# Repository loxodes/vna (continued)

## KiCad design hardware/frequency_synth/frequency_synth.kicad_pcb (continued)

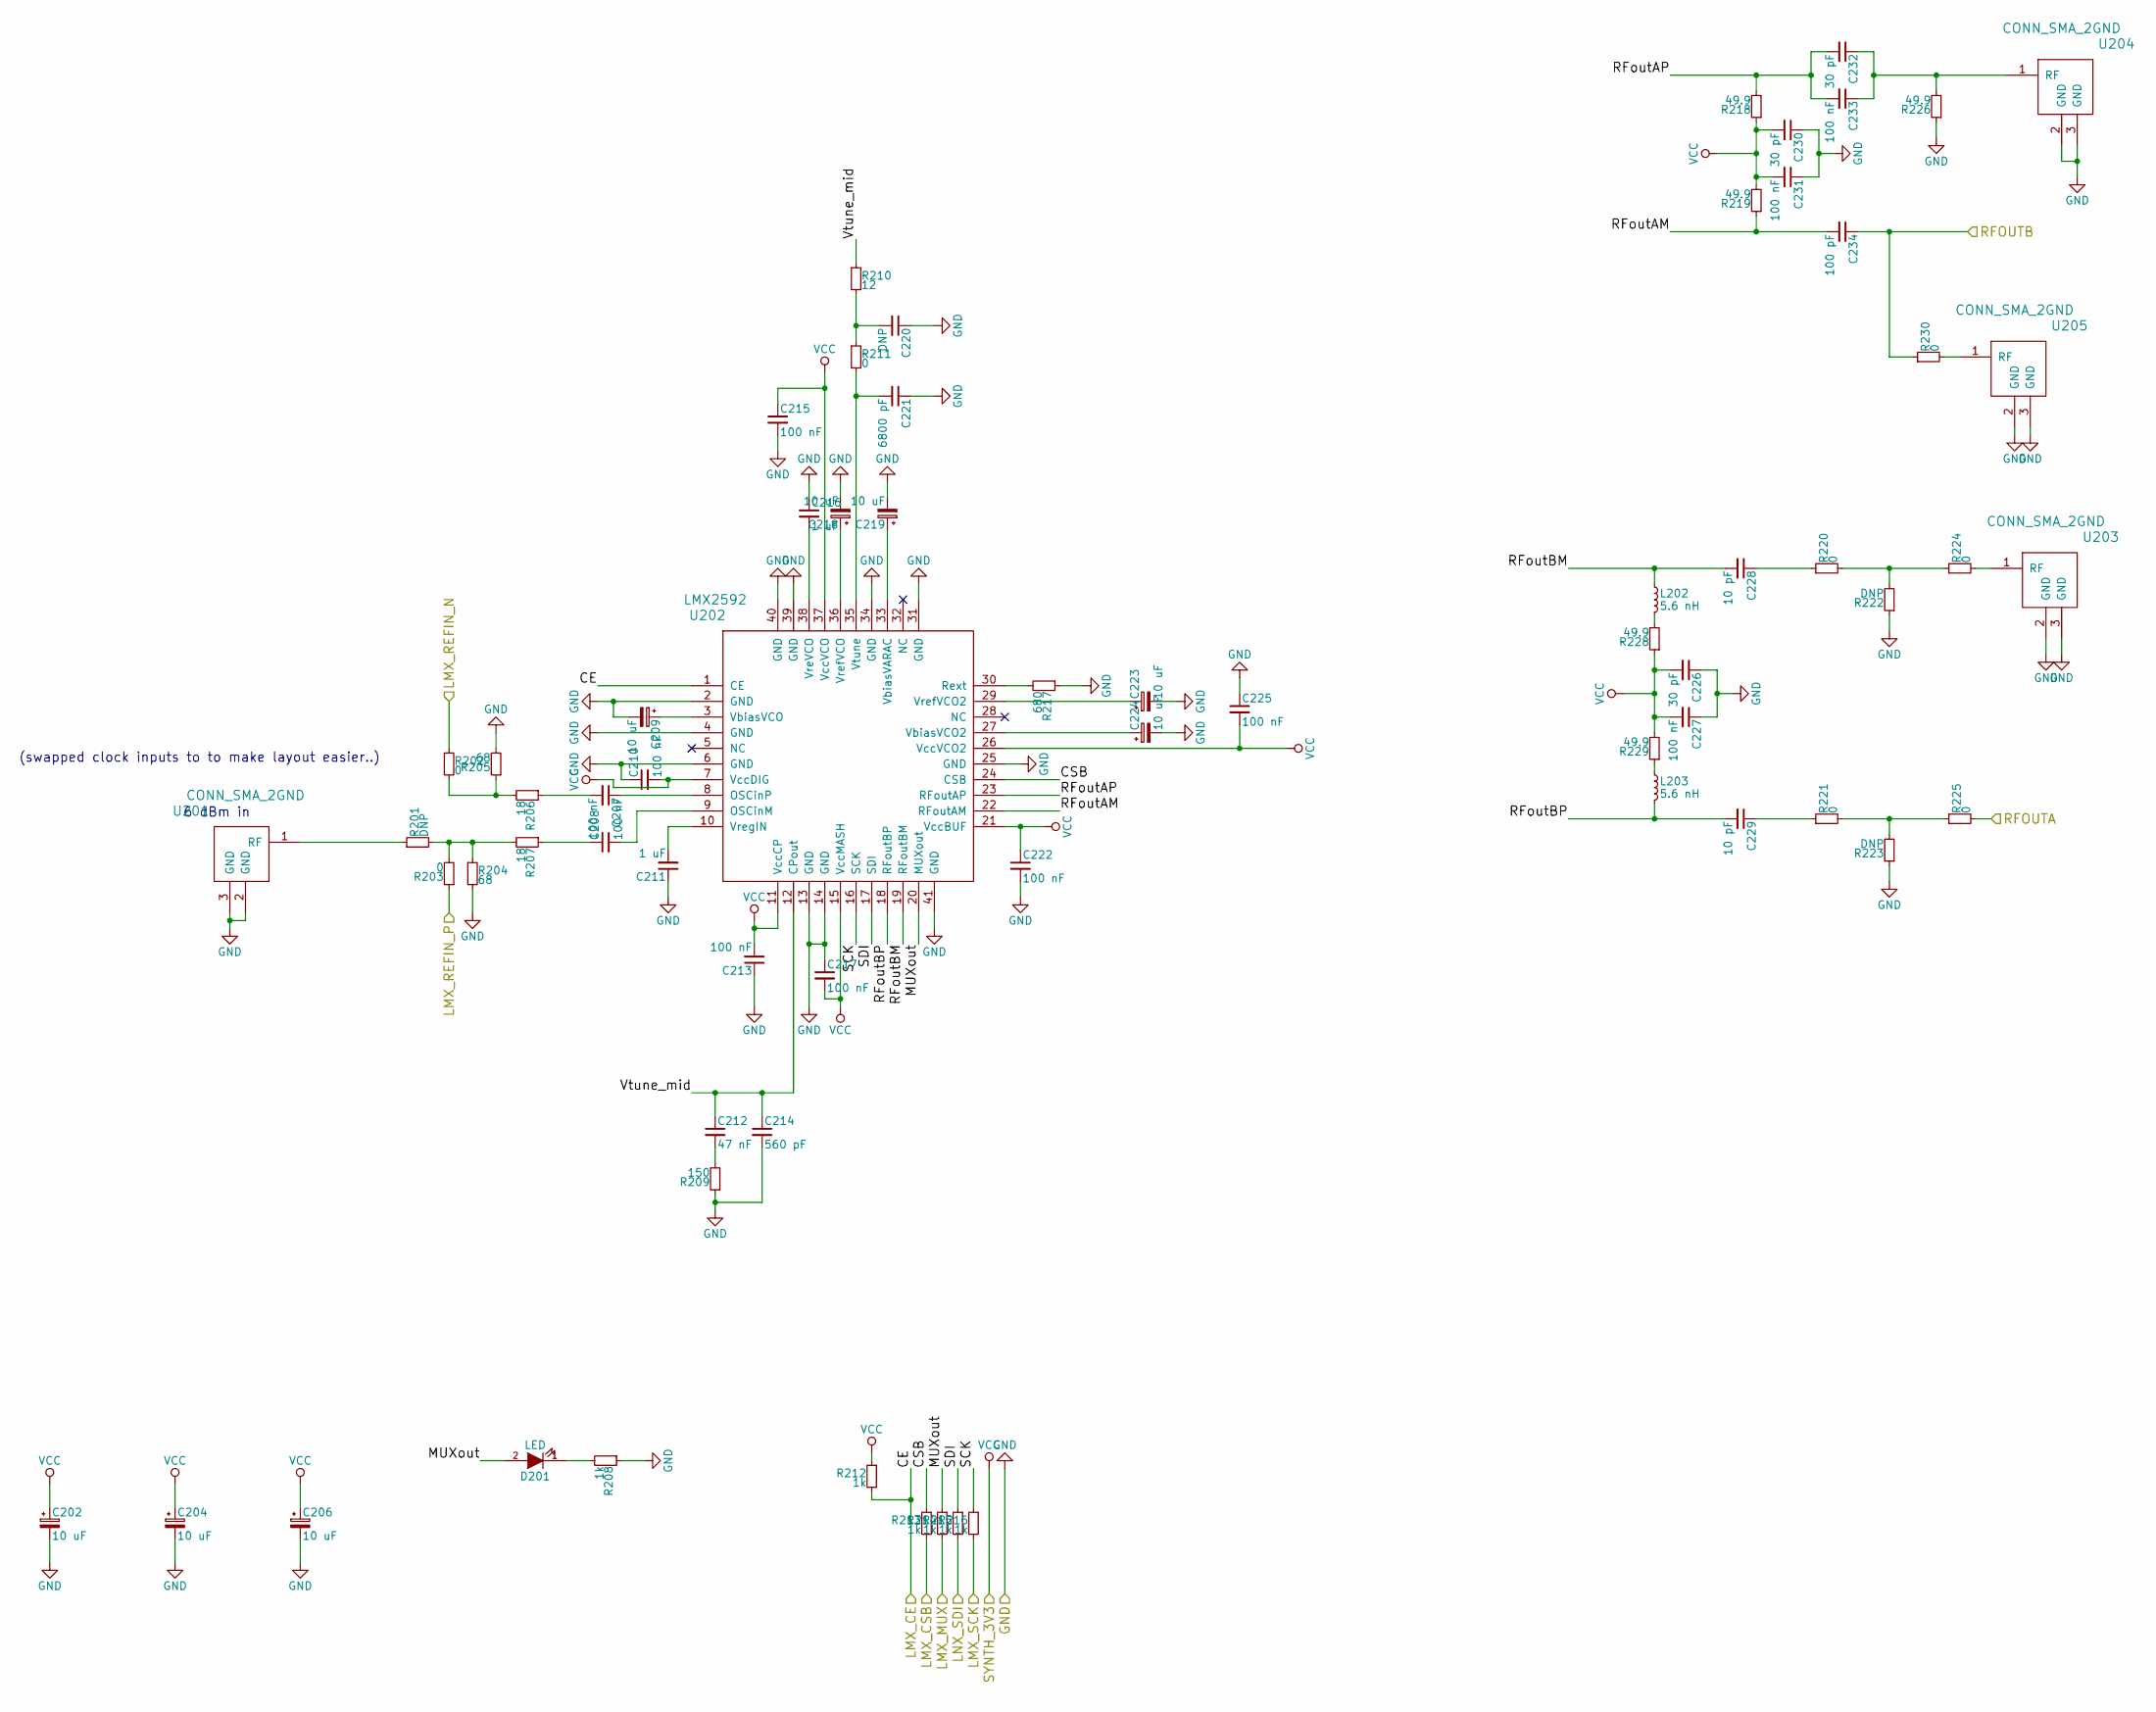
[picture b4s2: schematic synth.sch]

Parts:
C202, C204, C206, C209, C218, C219, C223, C224: 10 uF; C_0603
C207, C208, C210, C213, C215, C217, C222, C225, C227, C231, C233: 100 nF; C_0402
C211, C216: 1 uF; C_0402
C212: 47 nF; C_0402
C214: 560 pF; C_0402
C220: DNP; C_0402
C221: 6800 pF; C_0402
C226, C230, C232: 30 pF; C_0402
C228, C229: 10 pF; C_0402
C234: 100 pF; C_0402
D201: LED; LED_0603
L202, L203: 5.6 nH; R_0402
R201, R222, R223: DNP; R_0402
R202, R203, R211, R220, R221, R224, R225, R230: 0; R_0402
R204, R205: 68; R_0402
R206, R207: 18; R_0402
R208, R212, R213, R214, R215, R216: 1k; R_0402
R209: 150; R_0402
R210: 12; R_0402
R217: 680; R_0402
R218, R219, R226, R228, R229: 49.9; R_0402
U201, U203, U204, U205: CONN_SMA_2GND; 734120110_ufl_umc
U202: LMX2592; QFN-40-1EP_6x6mm_Pitch0.5mm

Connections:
+3V3: C202.1, C204.1, C206.1, C210.2, C213.2, C215.1, C217.2, C222.1, C225.2, C226.2, C227.2, C230.2, C231.2, R212.1, R218.1, R219.2, R228.1, R229.2, U202.7 (VccDIG), U202.11 (VccCP), U202.15 (VccMASH), U202.21 (VccBUF), U202.26 (VccVCO2), U202.37 (VccVCO); also elsewhere on the board
/LMX_CE: R212.2, U202.1 (CE); also elsewhere on the board
/LMX_CSB: R213.2; also elsewhere on the board
/LMX_MUX: R214.2; also elsewhere on the board
/LMX_SCK: R216.2; also elsewhere on the board
/LMX_SDI: R215.2; also elsewhere on the board
/filter bank/FILT_RFIN: C234.1, R230.1; also elsewhere on the board
/frequency_synth/CSB: R213.1, U202.24 (CSB)
/frequency_synth/LMX_REFIN_N: R202.1; also elsewhere on the board
/frequency_synth/LMX_REFIN_P: R203.1; also elsewhere on the board
/frequency_synth/MUXout: D201.2 (A), R214.1, U202.20 (MUXout)
/frequency_synth/RFOUTA: R225.2; also elsewhere on the board
/frequency_synth/RFoutAM: C234.2, R219.1, U202.22 (RFoutAM)
/frequency_synth/RFoutAP: C232.2, C233.2, R218.2, U202.23 (RFoutAP)
/frequency_synth/RFoutBM: C228.2, L202.1, U202.19 (RFoutBM)
/frequency_synth/RFoutBP: C229.2, L203.2, U202.18 (RFoutBP)
/frequency_synth/SCK: R216.1, U202.16 (SCK)
/frequency_synth/SDI: R215.1, U202.17 (SDI)
/frequency_synth/Vtune_mid: C212.1, C214.1, R210.1, U202.12 (CPout)
GND: C202.2, C204.2, C206.2, C209.2, C210.1, C211.1, C213.1, C214.2, C215.2, C216.1, C217.1, C218.2, C219.2, C220.1, C221.1, C222.2, C223.2, C224.2, C225.1, C226.1, C227.1, C230.1, C231.1, R204.2, R205.2, R208.1, R209.1, R217.1, R222.1, R223.1, R226.1, U201.2 (GND), U201.3 (GND), U202.2 (GND), U202.4 (GND), U202.6 (GND), U202.13 (GND), U202.14 (GND), U202.25 (GND), U202.31 (GND), U202.34 (GND), U202.39 (GND), U202.40 (GND), U202.41 (GND), U203.2 (GND), U203.3 (GND), U204.2 (GND), U204.3 (GND), U205.2 (GND), U205.3 (GND); also elsewhere on the board
unnamed: C207.1, U202.8 (OSCinP)
unnamed: C207.2, R206.1
unnamed: C208.1, R207.1
unnamed: C208.2, U202.9 (OSCinM)
unnamed: C209.1, U202.3 (VbiasVCO)
unnamed: C211.2, U202.10 (VregIN)
unnamed: C212.2, R209.2
unnamed: C216.2, U202.38 (VreVCO)
unnamed: C218.1, U202.36 (VrefVCO)
unnamed: C219.1, U202.33 (VbiasVARAC)
unnamed: C220.2, R210.2, R211.1
unnamed: C221.2, R211.2, U202.35 (Vtune)
unnamed: C223.1, U202.29 (VrefVCO2)
unnamed: C224.1, U202.27 (VbiasVCO2)
unnamed: C228.1, R220.1
unnamed: C229.1, R221.1
unnamed: C232.1, C233.1, R226.2, U204.1 (RF)
unnamed: D201.1 (K), R208.2
unnamed: L202.2, R228.2
unnamed: L203.1, R229.1
unnamed: R201.1, U201.1 (RF)
unnamed: R201.2, R203.2, R204.1, R207.2
unnamed: R202.2, R205.1, R206.2
unnamed: R217.2, U202.30 (Rext)
unnamed: R220.2, R222.2, R224.1
unnamed: R221.2, R223.2, R225.1
unnamed: R224.2, U203.1 (RF)
unnamed: R230.2, U205.1 (RF)

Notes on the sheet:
6 dBm in
(swapped clock inputs to to make layout easier..)

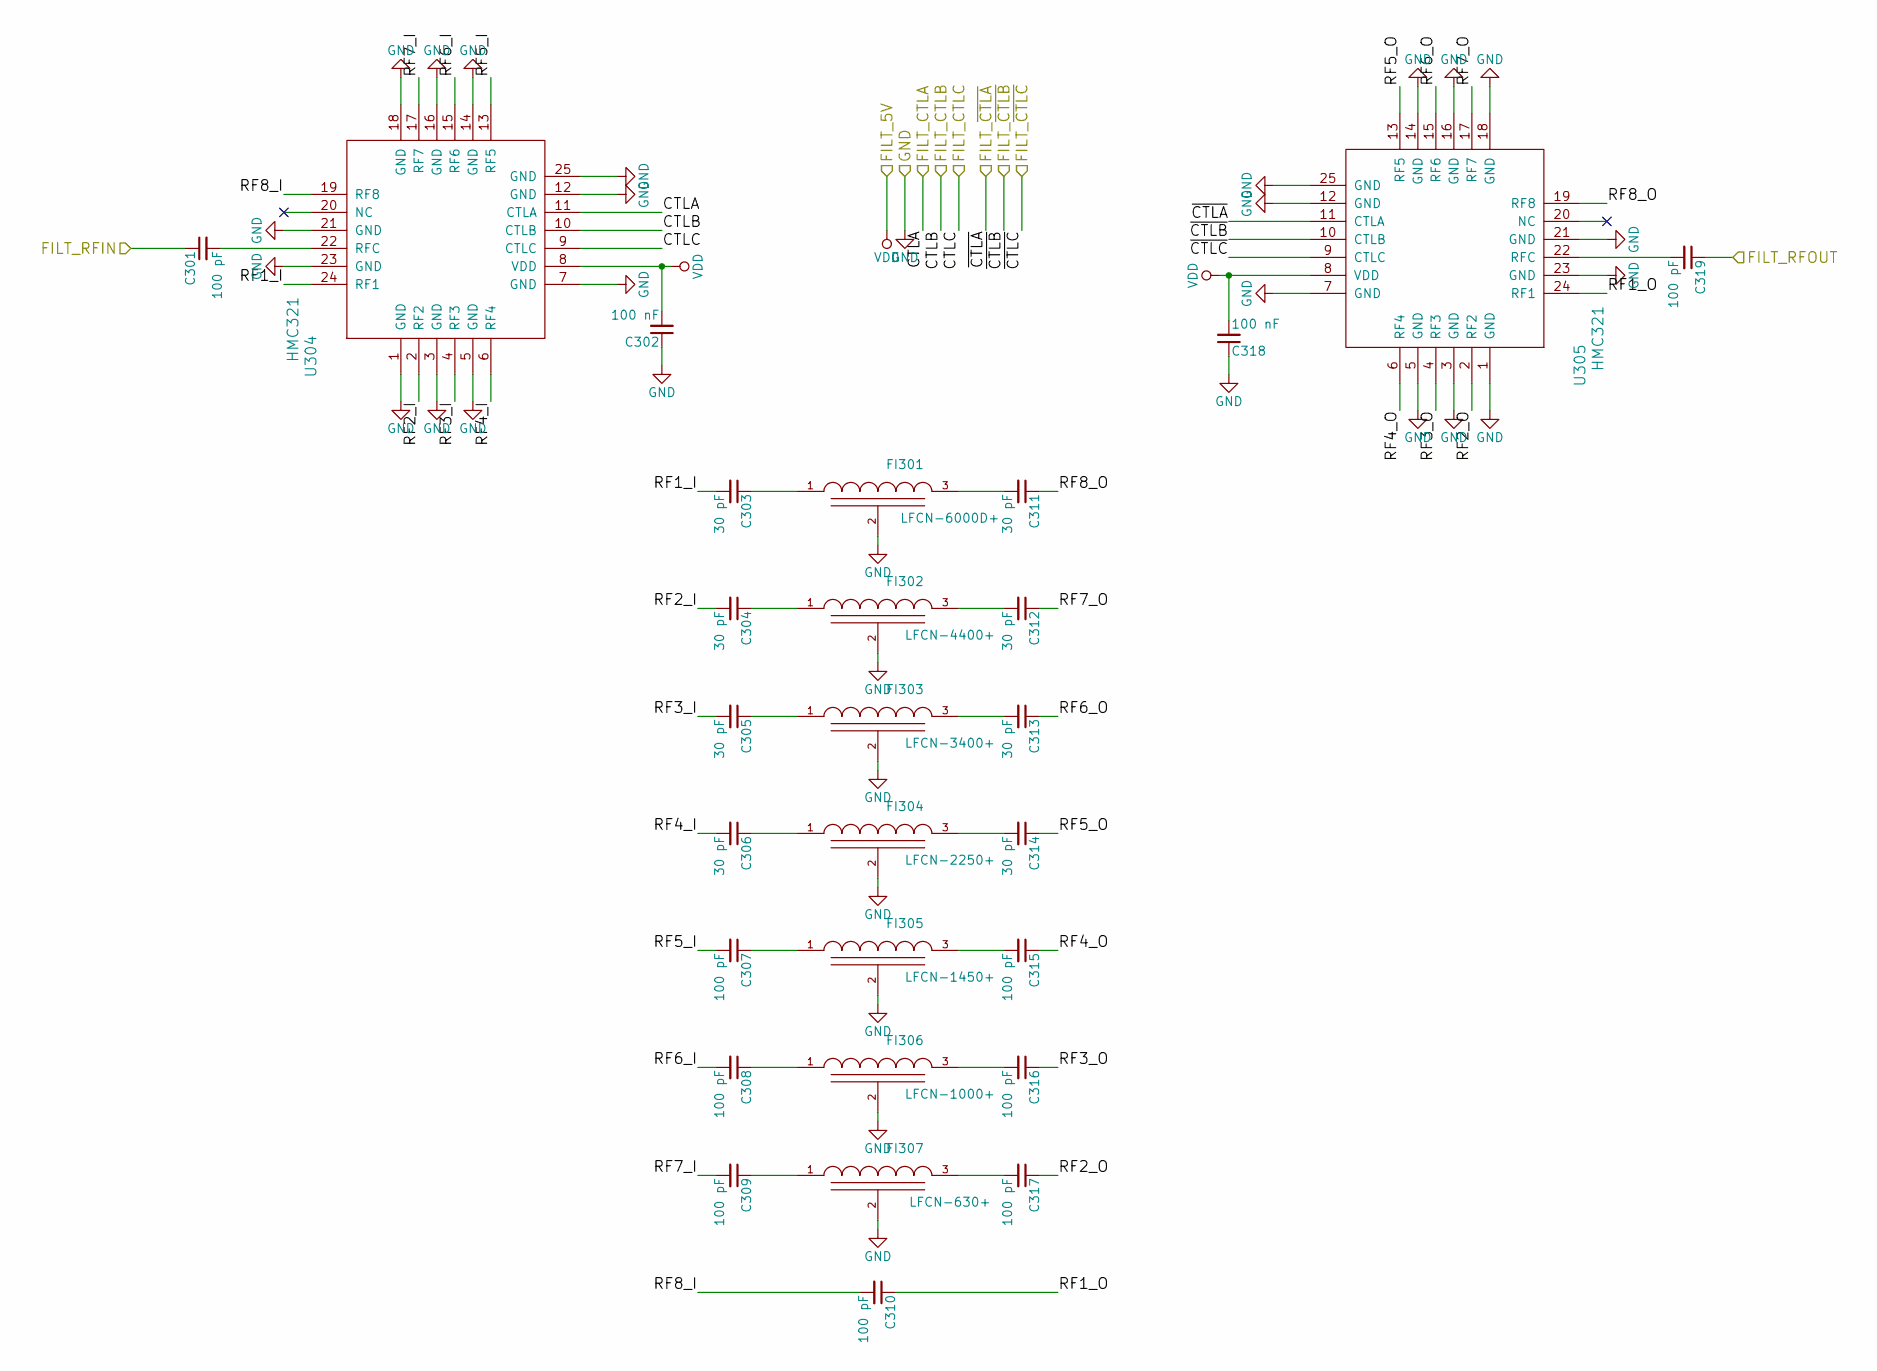
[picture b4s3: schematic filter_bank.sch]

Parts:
C301, C307, C308, C309, C310, C315, C316, C317, C319: 100 pF; C_0402
C302, C318: 100 nF; C_0402
C303, C304, C305, C306, C311, C312, C313, C314: 30 pF; C_0402
FI301: LFCN-6000D+; FV1206
FI302: LFCN-4400+; FV1206
FI303: LFCN-3400+; FV1206
FI304: LFCN-2250+; FV1206
FI305: LFCN-1450+; FV1206
FI306: LFCN-1000+; FV1206
FI307: LFCN-630+; FV1206
U304, U305: HMC321; QFN-24-1EP_4x4mm_Pitch0.5mm

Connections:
+5V: C302.2, C318.2, U304.8 (VDD), U305.8 (VDD); also elsewhere on the board
/FILT_A: U304.11 (CTLA); also elsewhere on the board
/FILT_B: U304.10 (CTLB); also elsewhere on the board
/FILT_C: U304.9 (CTLC); also elsewhere on the board
/FILT_~A: U305.11 (CTLA); also elsewhere on the board
/FILT_~B: U305.10 (CTLB); also elsewhere on the board
/FILT_~C: U305.9 (CTLC); also elsewhere on the board
/filter bank/FILT_RFIN: C301.1; also elsewhere on the board
/filter bank/FILT_RFOUT: C319.1; also elsewhere on the board
/filter bank/RF1_I: C303.2, U304.24 (RF1)
/filter bank/RF1_O: C310.1, U305.24 (RF1)
/filter bank/RF2_I: C304.2, U304.2 (RF2)
/filter bank/RF2_O: C317.1, U305.2 (RF2)
/filter bank/RF3_I: C305.2, U304.4 (RF3)
/filter bank/RF3_O: C316.1, U305.4 (RF3)
/filter bank/RF4_I: C306.2, U304.6 (RF4)
/filter bank/RF4_O: C315.1, U305.6 (RF4)
/filter bank/RF5_I: C307.2, U304.13 (RF5)
/filter bank/RF5_O: C314.1, U305.13 (RF5)
/filter bank/RF6_I: C308.2, U304.15 (RF6)
/filter bank/RF6_O: C313.1, U305.15 (RF6)
/filter bank/RF7_I: C309.2, U304.17 (RF7)
/filter bank/RF7_O: C312.1, U305.17 (RF7)
/filter bank/RF8_I: C310.2, U304.19 (RF8)
/filter bank/RF8_O: C311.1, U305.19 (RF8)
GND: C302.1, C318.1, FI301.2 (GND), FI302.2 (GND), FI303.2 (GND), FI304.2 (GND), FI305.2 (GND), FI306.2 (GND), FI307.2 (GND), U304.1 (GND), U304.3 (GND), U304.5 (GND), U304.7 (GND), U304.12 (GND), U304.14 (GND), U304.16 (GND), U304.18 (GND), U304.21 (GND), U304.23 (GND), U304.25 (GND), U305.1 (GND), U305.3 (GND), U305.5 (GND), U305.7 (GND), U305.12 (GND), U305.14 (GND), U305.16 (GND), U305.18 (GND), U305.21 (GND), U305.23 (GND), U305.25 (GND); also elsewhere on the board
unnamed: C301.2, U304.22 (RFC)
unnamed: C303.1, FI301.1 (VI)
unnamed: C304.1, FI302.1 (VI)
unnamed: C305.1, FI303.1 (VI)
unnamed: C306.1, FI304.1 (VI)
unnamed: C307.1, FI305.1 (VI)
unnamed: C308.1, FI306.1 (VI)
unnamed: C309.1, FI307.1 (VI)
unnamed: C311.2, FI301.3 (VO)
unnamed: C312.2, FI302.3 (VO)
unnamed: C313.2, FI303.3 (VO)
unnamed: C314.2, FI304.3 (VO)
unnamed: C315.2, FI305.3 (VO)
unnamed: C316.2, FI306.3 (VO)
unnamed: C317.2, FI307.3 (VO)
unnamed: C319.2, U305.22 (RFC)

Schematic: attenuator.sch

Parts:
C401, C408: 30 pF; C_0402
C402, C407, C410: 100 nF; C_0402
C403, C404: 10 uF; C_0603
C405: 1 uF; C_0402
C406, C409: 100 pF; C_0402
D401, D402, D403, D404, D405, D406: 5.1V; SOD-123
R401, R402, R403, R410, R411, R412: 10k; R_0402
R404, R405, R406, R407, R408, R409: 100; R_0402
U401: LTC1983; SOT-23-6
U402: HMC424; QFN-16-1EP_3x3mm_Pitch0.5mm
U403: 74HC04_FULL; TSSOP-14_4.4x5mm_Pitch0.65mm

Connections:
+5V: C401.2, C402.2, C403.1, U401.1 (Vcc), U401.6 (~SHDN); also elsewhere on the board
/ATT_A1: D401.1 (K); also elsewhere on the board
/ATT_A2: D402.1 (K); also elsewhere on the board
/ATT_A3: D403.1 (K); also elsewhere on the board
/ATT_A4: D406.1 (K); also elsewhere on the board
/ATT_A5: D405.1 (K); also elsewhere on the board
/ATT_A6: D404.1 (K); also elsewhere on the board
/attenuator/ATT_RFIN: C406.2; also elsewhere on the board
/attenuator/ATT_RFOUT: C409.1; also elsewhere on the board
/attenuator/V1: R404.2, U402.9 (V1)
/attenuator/V2: R405.2, U402.8 (V2)
/attenuator/V3: R406.2, U402.7 (V3)
/attenuator/V4: R409.1, U402.6 (V4)
/attenuator/V5: R408.1, U402.5 (V5)
/attenuator/V6: R407.1, U402.4 (V6)
GND: C401.1, C402.1, C403.2, C404.2, C407.1, C408.1, C410.1, U401.5 (GND), U402.1 (GND), U402.3 (GND), U402.10 (GND), U402.12 (GND), U402.17 (GND), U403.14; also elsewhere on the board
unnamed: C405.1, U401.4 (Cm)
unnamed: C405.2, U401.3 (Cp)
unnamed: C406.1, U402.2 (RFIN)
unnamed: C409.2, U402.11 (RFOUT)
unnamed: D401.2 (A), R401.1, U403.1
unnamed: D402.2 (A), R402.1, U403.3
unnamed: D403.2 (A), R403.1, U403.5
unnamed: D404.2 (A), R412.1, U403.13
unnamed: D405.2 (A), R411.1, U403.11
unnamed: D406.2 (A), R410.1, U403.9
unnamed: R404.1, U403.2
unnamed: R405.1, U403.4
unnamed: R406.1, U403.6
unnamed: R407.2, U403.12
unnamed: R408.2, U403.10
unnamed: R409.2, U403.8
VEE: C404.1, C407.2, C408.2, C410.2, R401.2, R402.2, R403.2, R410.2, R411.2, R412.2, U401.2 (Vout), U402.15 (VEE), U403.7

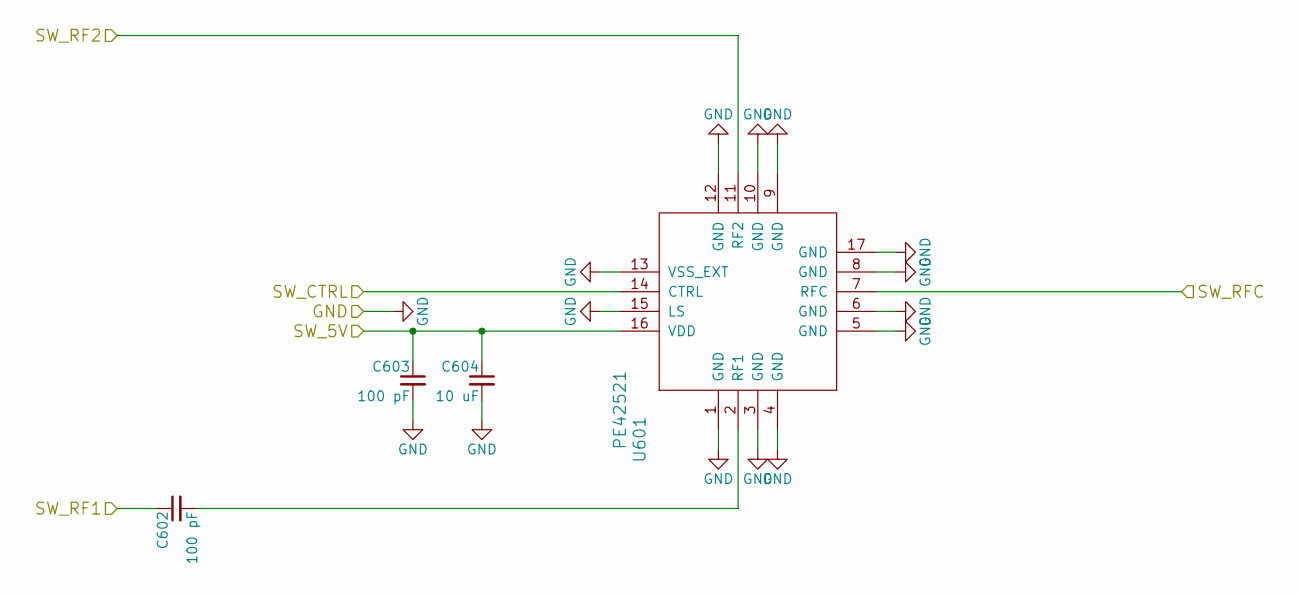
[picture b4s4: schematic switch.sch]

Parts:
C602, C603: 100 pF; C_0402
C604: 10 uF; C_0603
U601: PE42521; QFN-16-1EP_3x3mm_Pitch0.5mm

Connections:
+5V: C603.1, C604.1, U601.16 (VDD); also elsewhere on the board
/SW_CTL: U601.14 (CTRL); also elsewhere on the board
/attenuator/ATT_RFIN: U601.7 (RFC); also elsewhere on the board
/filter bank/FILT_RFOUT: U601.11 (RF2); also elsewhere on the board
/switch/SW_RF1: C602.1; also elsewhere on the board
GND: C603.2, C604.2, U601.1 (GND), U601.3 (GND), U601.4 (GND), U601.5 (GND), U601.6 (GND), U601.8 (GND), U601.9 (GND), U601.10 (GND), U601.12 (GND), U601.13 (VSS_EXT), U601.15 (LS), U601.17 (GND); also elsewhere on the board
unnamed: C602.2, U601.2 (RF1)

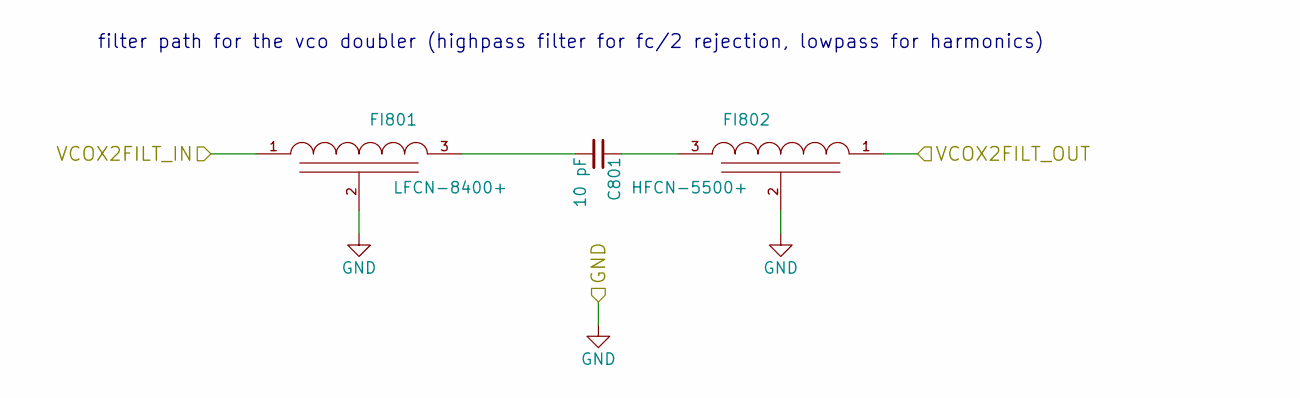
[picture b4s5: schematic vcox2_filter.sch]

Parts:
C801: 10 pF; C_0402
FI801: LFCN-8400+; FV1206
FI802: HFCN-5500+; FV1206-1

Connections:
/frequency_synth/RFOUTA: FI801.1 (VI); also elsewhere on the board
/switch/SW_RF1: FI802.1 (VI); also elsewhere on the board
GND: FI801.2 (GND), FI802.2 (GND); also elsewhere on the board
unnamed: C801.1, FI802.3 (VO)
unnamed: C801.2, FI801.3 (VO)

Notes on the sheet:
filter path for the vco doubler (highpass filter for fc/2 rejection, lowpass for harmonics)

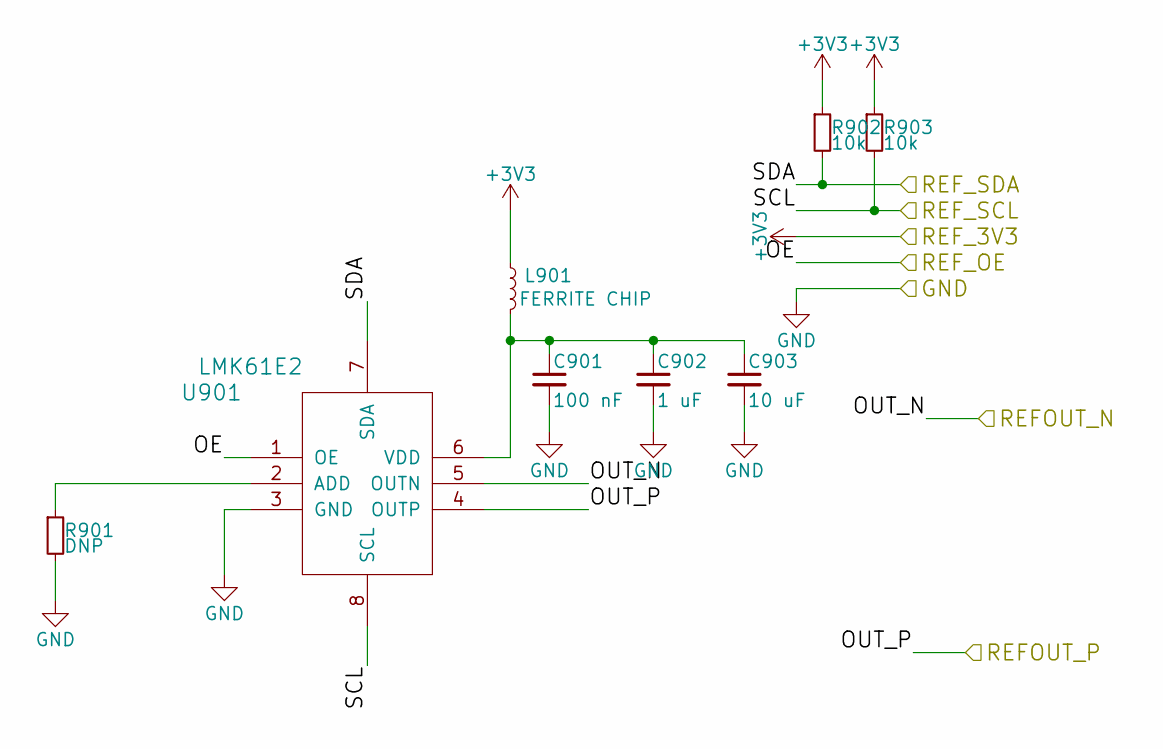
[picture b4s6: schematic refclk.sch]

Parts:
C901: 100 nF; C_0402
C902: 1 uF; C_0402
C903: 10 uF; C_0603
L901: FERRITE CHIP; R_0603
R901: DNP; R_0402
R902, R903: 10k; R_0402
U901: LMK61E2; QFM8

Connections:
+3V3: L901.1, R902.1, R903.1; also elsewhere on the board
/REF_OE: U901.1 (OE); also elsewhere on the board
/REF_SCL: R903.2, U901.8 (SCL); also elsewhere on the board
/REF_SDA: R902.2, U901.7 (SDA); also elsewhere on the board
/frequency_synth/LMX_REFIN_N: U901.5 (OUTN); also elsewhere on the board
/frequency_synth/LMX_REFIN_P: U901.4 (OUTP); also elsewhere on the board
GND: C901.2, C902.2, C903.2, R901.2, U901.3 (GND); also elsewhere on the board
unnamed: C901.1, C902.1, C903.1, L901.2, U901.6 (VDD)
unnamed: R901.1, U901.2 (ADD)

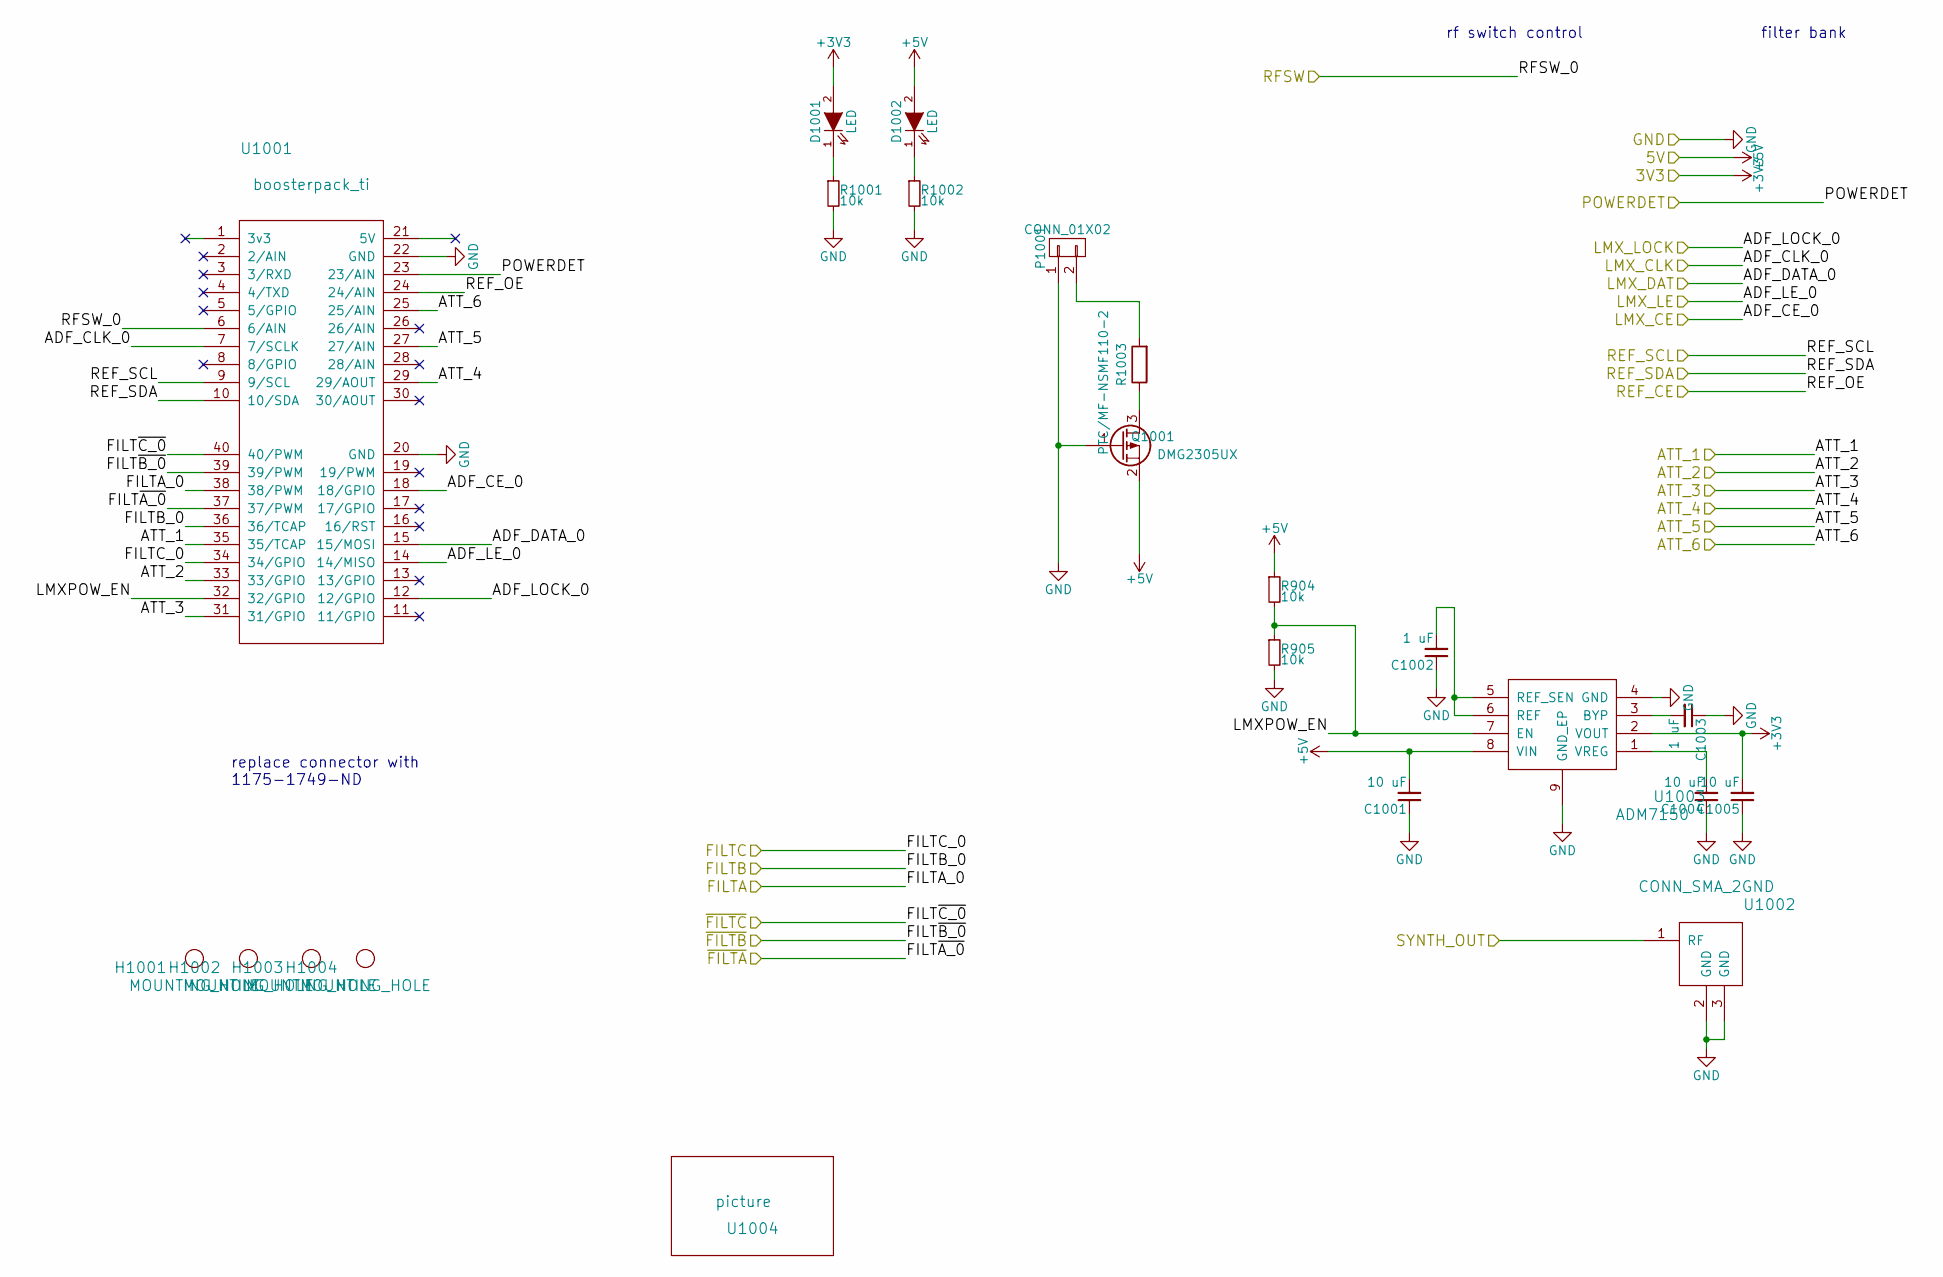
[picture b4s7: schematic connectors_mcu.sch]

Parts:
C1001, C1004, C1005: 10 uF; C_0603
C1002, C1003: 1 uF; C_0402
D1001, D1002: LED; LED_0603
H1001, H1002, H1003, H1004: MOUNTING_HOLE; MountingHole_2-7mm
P1001: CONN_01X02; TerminalBlock_Pheonix_PT-3.5mm_2pol
Q1001: DMG2305UX; SOT-23
R904, R905, R1001, R1002: 10k; R_0402
R1003: PTC/MF-NSMF110-2; R_1206
U1001: boosterpack_ti; 3221-40-0100-00_conn40
U1002: CONN_SMA_2GND; SMA_CPW_1MM_.2MM
U1003: ADM7150; DFN-8-1EP_3x3mm_Pitch0.5mm
U1004: picture; cat

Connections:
+3V3: C1005.2, D1001.2 (A), U1003.2 (VOUT); also elsewhere on the board
+5V: C1001.2, D1002.2 (A), Q1001.2 (S), R904.1, U1003.8 (VIN); also elsewhere on the board
/ATT_A1: U1001.35 (35/TCAP); also elsewhere on the board
/ATT_A2: U1001.33 (33/GPIO); also elsewhere on the board
/ATT_A3: U1001.31 (31/GPIO); also elsewhere on the board
/ATT_A4: U1001.29 (29/AOUT); also elsewhere on the board
/ATT_A5: U1001.27 (27/AIN); also elsewhere on the board
/ATT_A6: U1001.25 (25/AIN); also elsewhere on the board
/FILT_A: U1001.38 (38/PWM); also elsewhere on the board
/FILT_B: U1001.36 (36/TCAP); also elsewhere on the board
/FILT_C: U1001.34 (34/GPIO); also elsewhere on the board
/FILT_~A: U1001.37 (37/PWM); also elsewhere on the board
/FILT_~B: U1001.39 (39/PWM); also elsewhere on the board
/FILT_~C: U1001.40 (40/PWM); also elsewhere on the board
/LMX_CE: U1001.18 (18/GPIO); also elsewhere on the board
/LMX_CSB: U1001.14 (14/MISO); also elsewhere on the board
/LMX_MUX: U1001.12 (12/GPIO); also elsewhere on the board
/LMX_SCK: U1001.7 (7/SCLK); also elsewhere on the board
/LMX_SDI: U1001.15 (15/MOSI); also elsewhere on the board
/REF_OE: U1001.24 (24/AIN); also elsewhere on the board
/REF_SCL: U1001.9 (9/SCL); also elsewhere on the board
/REF_SDA: U1001.10 (10/SDA); also elsewhere on the board
/SW_CTL: U1001.6 (6/AIN); also elsewhere on the board
/attenuator/ATT_RFOUT: U1002.1 (RF); also elsewhere on the board
/connectors, microcontroller, psu/LMXPOW_EN: R904.2, R905.1, U1001.32 (32/GPIO), U1003.7 (EN)
GND: C1001.1, C1002.1, C1003.1, C1004.1, C1005.1, P1001.1, Q1001.1 (G), R905.2, R1001.2, R1002.2, U1001.20 (GND), U1001.22 (GND), U1002.2 (GND), U1002.3 (GND), U1003.4 (GND), U1003.9 (GND_EP); also elsewhere on the board
unnamed: C1002.2, U1003.5 (REF_SEN), U1003.6 (REF)
unnamed: C1003.2, U1003.3 (BYP)
unnamed: C1004.2, U1003.1 (VREG)
unnamed: D1001.1 (K), R1001.1
unnamed: D1002.1 (K), R1002.1
unnamed: P1001.2, R1003.2
unnamed: Q1001.3 (D), R1003.1

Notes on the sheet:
filter bank
rf switch control
replace connector with 1175-1749-ND

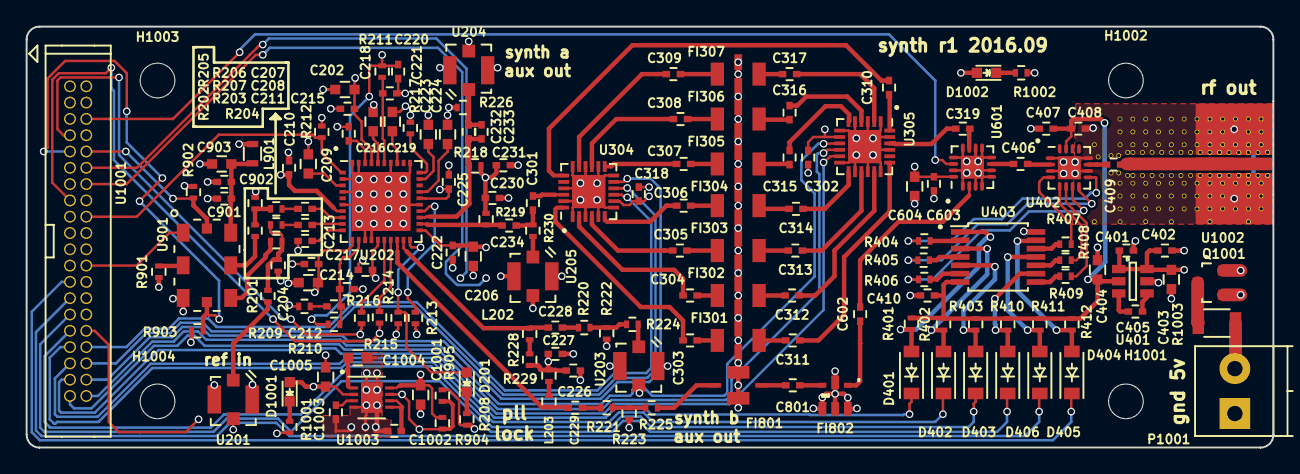
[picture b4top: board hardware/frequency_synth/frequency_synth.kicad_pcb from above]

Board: 4 copper layers, 97.1 x 32.8 mm, 164 parts (1 on the bottom side), 137 nets.

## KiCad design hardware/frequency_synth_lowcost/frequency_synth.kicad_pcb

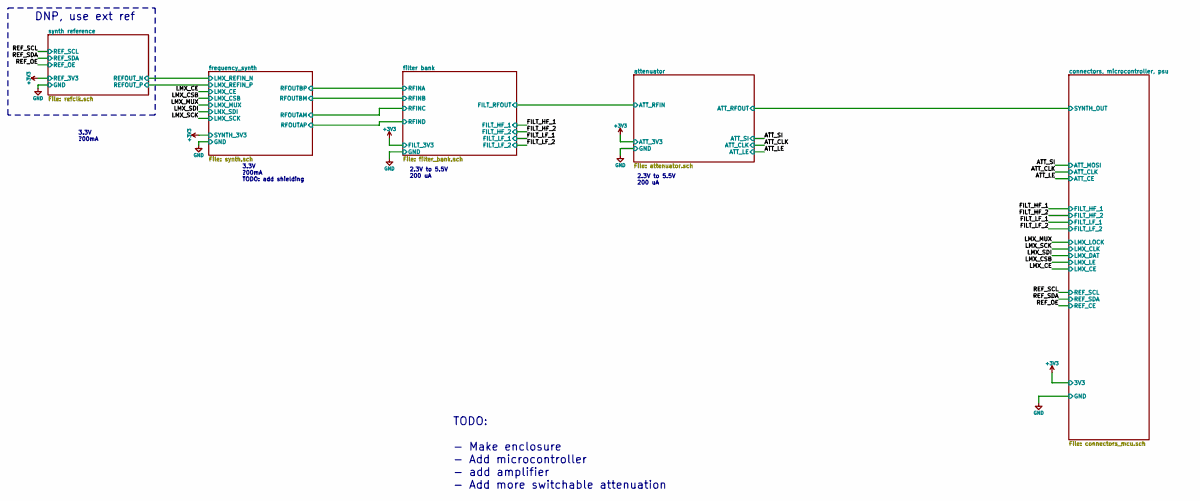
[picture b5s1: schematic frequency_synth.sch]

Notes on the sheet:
TODO: - Make enclosure - Add microcontroller - add amplifier - Add more switchable attenuation
DNP, use ext ref
2.3V to 5.5V 200 uA
3.3V ?00mA TODO: add shielding
3.3V ?00mA
